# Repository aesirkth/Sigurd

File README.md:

# Sigurd
Propulsion Sensor Unit

# Prerequisites
Follow [zephyr getting started guide](https://docs.zephyrproject.org/latest/develop/getting_started/index.html)

# Build 

```bash
cd zephyr-firmware
west update
cd sigurd
west build -b sigurd app --pristine
west flash
```

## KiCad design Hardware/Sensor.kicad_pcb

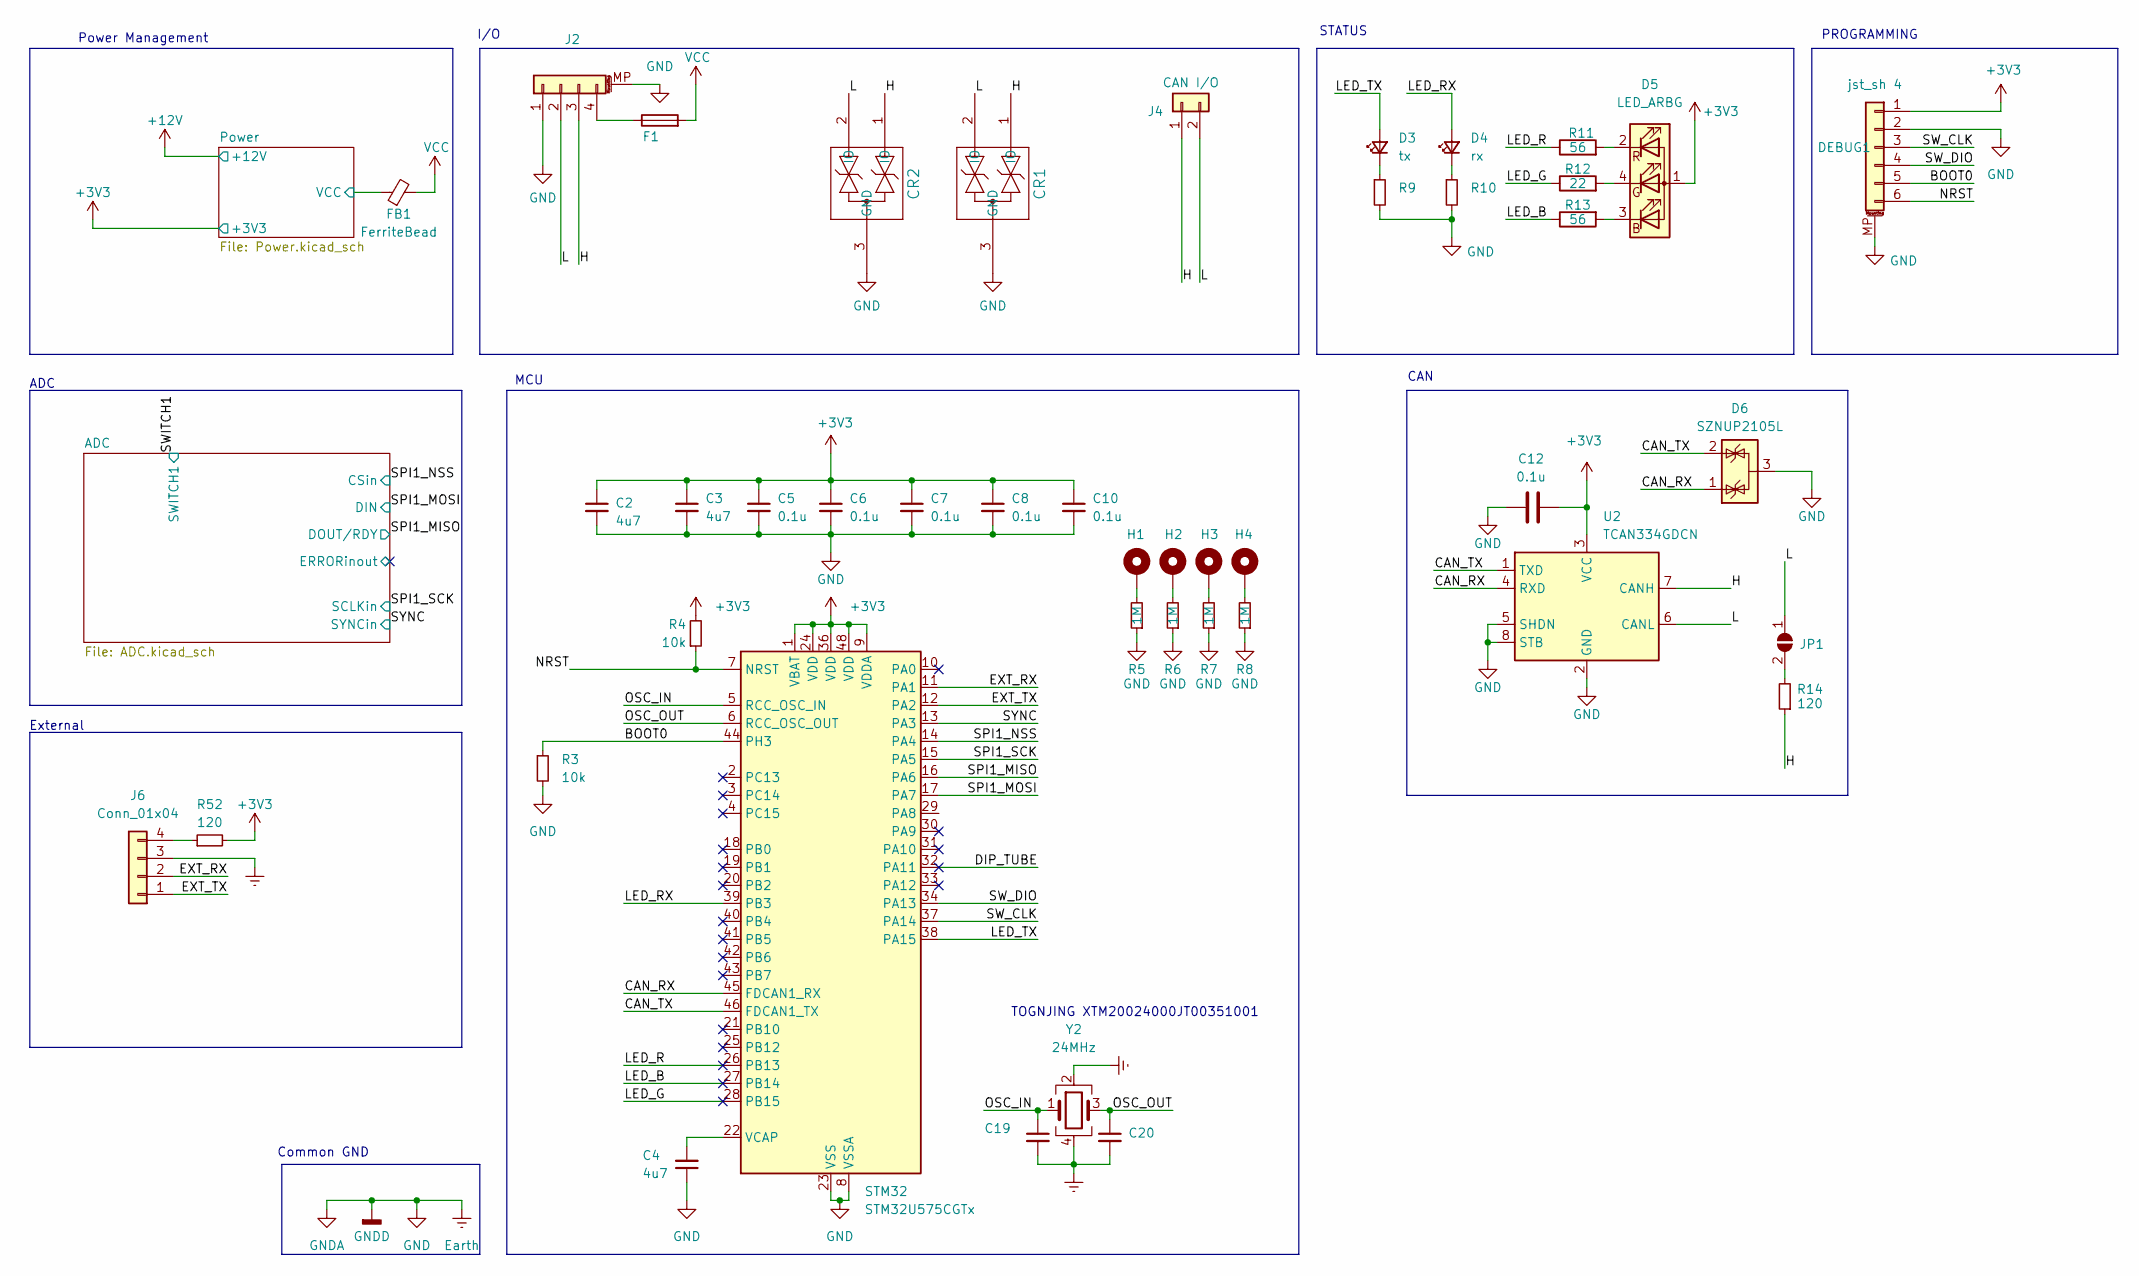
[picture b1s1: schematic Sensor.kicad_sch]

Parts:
C2, C3, C4: 4u7; C_0402_1005Metric
C5, C6, C7, C8, C10, C12: 0.1u; C_0402_1005Metric
C19, C20: 18p; C_0402_1005Metric
CR1, CR2: ESD2CAN36DBZRQ1; SOT-23-3
D3: tx; LED_0603_1608Metric_Pad1.05x0.95mm_HandSolder
D4: rx; LED_0603_1608Metric_Pad1.05x0.95mm_HandSolder
D5: LED_ARBG; LED_Lumex_SML-LX0404SIUPGUSB
D6: SZNUP2105L; SOT-23
DEBUG1: jst_sh 4; JST_SH_SM06B-SRSS-TB_1x06-1MP_P1.00mm_Horizontal
F1: Fuse_1206_3216Metric
FB1: FerriteBead; L_0603_1608Metric
H1, H2, H3, H4: MountingHole_Pad; MountingHole_3.2mm_M3_Pad_Via
J2: Conn_01x04_MountingPin; JST_GH_BM04B-GHS-TBT_1x04-1MP_P1.25mm_Vertical
J4: CAN I/O; JST_XH_B2B-XH-A_1x02_P2.50mm_Vertical
J6: Conn_01x04; PinSocket_1x04_P1.27mm_Vertical
JP1: SolderJumper_2_Open; SolderJumper-2_P1.3mm_Open_TrianglePad1.0x1.5mm
R3, R4: 10k; R_0402_1005Metric
R5, R6, R7, R8: 1M; R_0603_1608Metric_Pad0.98x0.95mm_HandSolder
R9, R10: 330; R_0603_1608Metric_Pad0.98x0.95mm_HandSolder
R11, R13: 56; R_0603_1608Metric_Pad0.98x0.95mm_HandSolder
R12: 22; R_0603_1608Metric_Pad0.98x0.95mm_HandSolder
R14: 120; R_0603_1608Metric_Pad0.98x0.95mm_HandSolder
R52: 120; R_0402_1005Metric
STM32: STM32U575CGTx; LQFP-48_7x7mm_P0.5mm
U2: TCAN334GDCN; TSOT-23-8
Y2: 24MHz; Crystal_SMD_2016-4Pin_2.0x1.6mm

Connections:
+3V3: C2.1, C3.1, C5.1, C6.1, C7.1, C8.1, C10.1, C12.2, D5.1 (A), DEBUG1.1, R4.2, R52.2, STM32.1 (VBAT), STM32.9 (VDDA), STM32.24 (VDD), STM32.36 (VDD), STM32.48 (VDD), U2.3 (VCC); also elsewhere on the board
+12V: FB1.1; also elsewhere on the board
/BOOT0: DEBUG1.5, R3.1, STM32.44 (PH3)
/CAN_RX: D6.1 (K), STM32.45 (FDCAN1_RX), U2.4 (RXD)
/CAN_TX: D6.2 (K), STM32.46 (FDCAN1_TX), U2.1 (TXD)
/DIP_TUBE: STM32.32 (PA11)
/EXT_RX: J6.2, STM32.11 (PA1)
/EXT_TX: J6.1, STM32.12 (PA2)
/H: CR1.1 (IO), CR2.1 (IO), J2.3, J4.1, R14.1, U2.7 (CANH)
/L: CR1.2 (IO), CR2.2 (IO), J2.2, J4.2, JP1.1 (A), U2.6 (CANL)
/LED_B: R13.1, STM32.27 (PB14)
/LED_G: R12.1, STM32.28 (PB15)
/LED_R: R11.1, STM32.26 (PB13)
/LED_RX: D4.2 (A), STM32.39 (PB3)
/LED_TX: D3.2 (A), STM32.38 (PA15)
/NRST: DEBUG1.6, R4.1, STM32.7 (NRST)
/OSC_IN: C19.1, STM32.5 (RCC_OSC_IN), Y2.1
/OSC_OUT: C20.1, STM32.6 (RCC_OSC_OUT), Y2.3
/SPI1_MISO: STM32.16 (PA6); also elsewhere on the board
/SPI1_MOSI: STM32.17 (PA7); also elsewhere on the board
/SPI1_NSS: STM32.14 (PA4); also elsewhere on the board
/SPI1_SCK: STM32.15 (PA5); also elsewhere on the board
/SW_CLK: DEBUG1.3, STM32.37 (PA14)
/SW_DIO: DEBUG1.4, STM32.34 (PA13)
/SYNC: STM32.13 (PA3); also elsewhere on the board
Earth: C2.2, C3.2, C4.1, C5.2, C6.2, C7.2, C8.2, C10.2, C12.1, C19.2, C20.2, CR1.3 (GND), CR2.3 (GND), D6.3 (A), DEBUG1.2, DEBUG1.MP (MountPin), J2.1, J2.MP (MountPin), J6.3, R3.2, R5.1, R6.1, R7.1, R8.1, R9.2, R10.2, STM32.8 (VSSA), STM32.23 (VSS), STM32.35 (VSS), STM32.47 (VSS), U2.2 (GND), U2.5 (SHDN), U2.8 (STB), Y2.2, Y2.4; also elsewhere on the board
unnamed: D3.1 (K), R9.1
unnamed: D4.1 (K), R10.1
unnamed: D5.3 (BK), R13.2
unnamed: D5.4 (GK), R12.2
unnamed: D5.2 (RK), R11.2
unnamed: H1.1, R5.2
unnamed: H2.1, R6.2
unnamed: H3.1, R7.2
unnamed: H4.1, R8.2
unnamed: F1.1, J2.4
unnamed: J6.4, R52.1
unnamed: JP1.2 (B), R14.2
unnamed: C4.2, STM32.22 (VCAP)
VCC: F1.2, FB1.2

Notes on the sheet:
MCU
PROGRAMMING
External
STATUS
CAN
ADC
I/O
Power Management
Common GND
TOGNJING XTM20024000JT00351001

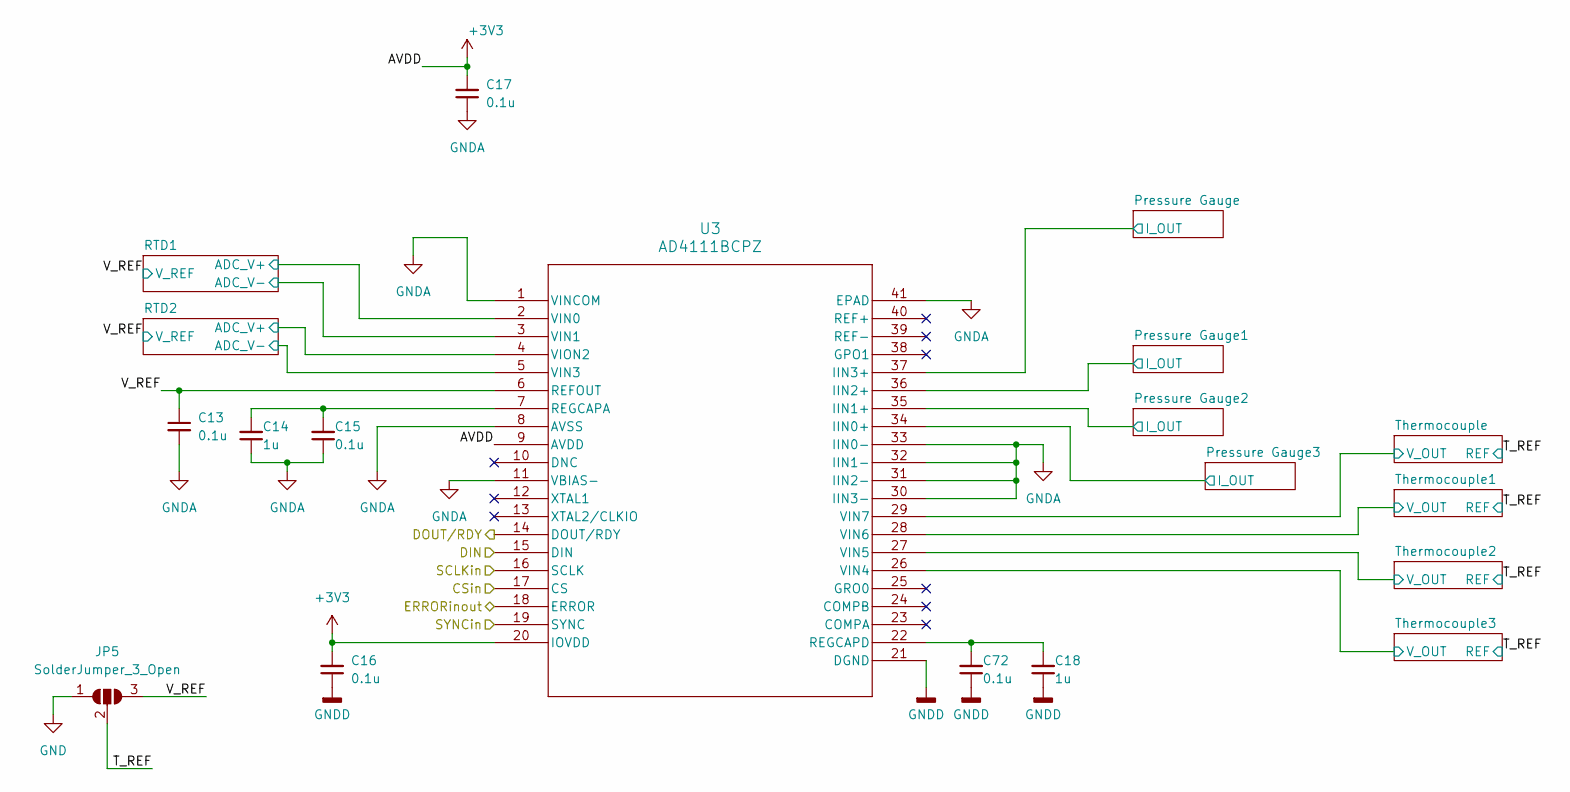
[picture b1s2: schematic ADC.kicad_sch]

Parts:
C13, C15, C16, C17, C72: 0.1u; C_0402_1005Metric
C14, C18: 1u; C_0402_1005Metric
JP5: SolderJumper_3_Open; SolderJumper-3_P1.3mm_Open_Pad1.0x1.5mm_NumberLabels
U3: AD4111BCPZ; AD4111BCPZ_ADI

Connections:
+3V3: C16.2, C17.2, U3.9 (AVDD), U3.20 (IOVDD); also elsewhere on the board
/ADC/ERRORinout: U3.18 (ERROR)
/ADC/Pressure Gauge1/I_OUT: U3.36 (IIN2+); also elsewhere on the board
/ADC/Pressure Gauge2/I_OUT: U3.35 (IIN1+); also elsewhere on the board
/ADC/Pressure Gauge3/I_OUT: U3.34 (IIN0+); also elsewhere on the board
/ADC/Pressure Gauge/I_OUT: U3.37 (IIN3+); also elsewhere on the board
/ADC/RTD1/ADC_V+: U3.2 (VIN0); also elsewhere on the board
/ADC/RTD1/ADC_V-: U3.3 (VIN1); also elsewhere on the board
/ADC/RTD2/ADC_V+: U3.4 (VION2); also elsewhere on the board
/ADC/RTD2/ADC_V-: U3.5 (VIN3); also elsewhere on the board
/ADC/T_REF: JP5.2 (C); also elsewhere on the board
/ADC/Thermocouple1/V_OUT: U3.28 (VIN6); also elsewhere on the board
/ADC/Thermocouple2/V_OUT: U3.27 (VIN5); also elsewhere on the board
/ADC/Thermocouple3/V_OUT: U3.26 (VIN4); also elsewhere on the board
/ADC/Thermocouple/V_OUT: U3.29 (VIN7); also elsewhere on the board
/ADC/V_REF: C13.1, JP5.3 (B), U3.6 (REFOUT); also elsewhere on the board
/SPI1_MISO: U3.14 (DOUT/RDY); also elsewhere on the board
/SPI1_MOSI: U3.15 (DIN); also elsewhere on the board
/SPI1_NSS: U3.17 (CS); also elsewhere on the board
/SPI1_SCK: U3.16 (SCLK); also elsewhere on the board
/SYNC: U3.19 (SYNC); also elsewhere on the board
Earth: C13.2, C14.1, C15.1, C16.1, C17.1, C18.1, C72.1, JP5.1 (A), U3.1 (VINCOM), U3.8 (AVSS), U3.11 (VBIAS-), U3.21 (DGND), U3.30 (IIN3-), U3.31 (IIN2-), U3.32 (IIN1-), U3.33 (IIN0-), U3.41 (EPAD); also elsewhere on the board
unnamed: C14.2, C15.2, U3.7 (REGCAPA)
unnamed: C18.2, C72.2, U3.22 (REGCAPD)

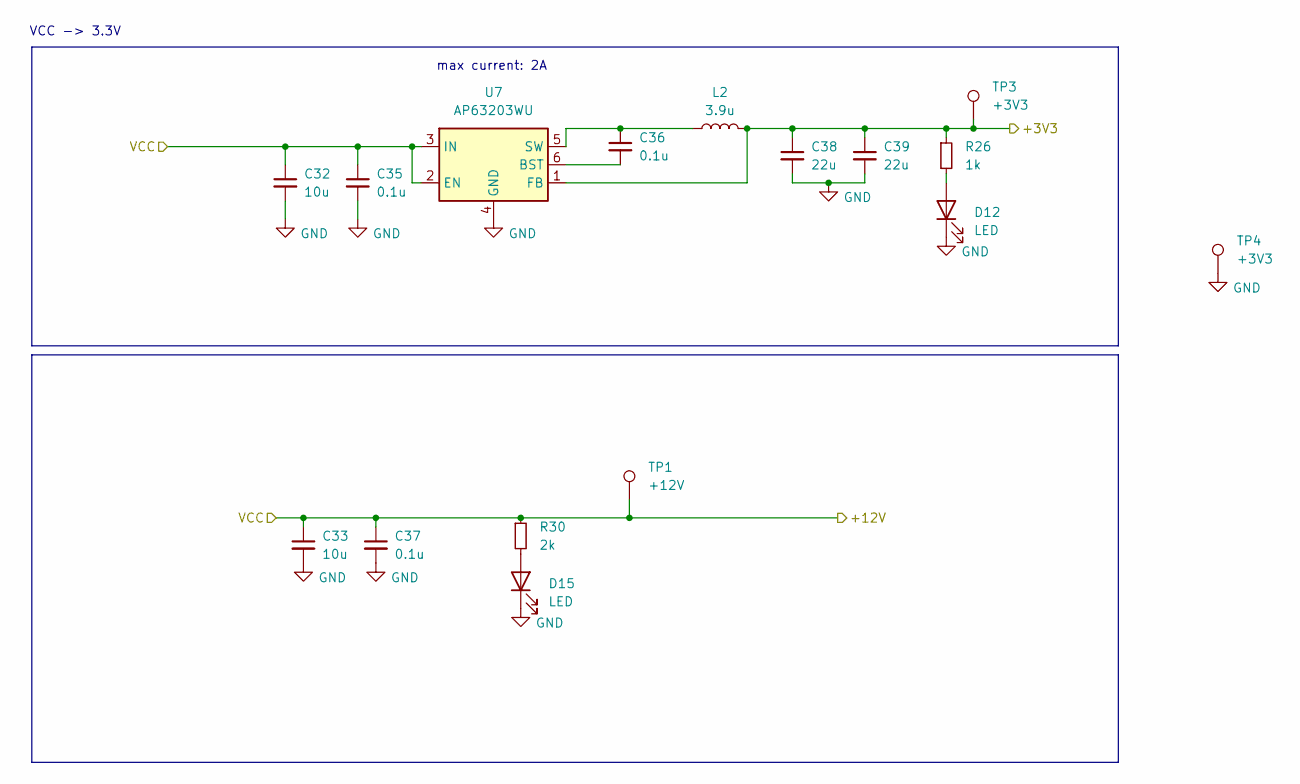
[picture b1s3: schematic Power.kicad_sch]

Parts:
C32, C33: 10u; C_0603_1608Metric
C35, C36, C37: 0.1u; C_0402_1005Metric
C38, C39: 22u; C_0603_1608Metric
D12, D15: LED; D_0603_1608Metric
L2: 3.9u; L_Changjiang_FNR4030S
R26: 1k; R_0603_1608Metric
R30: 2k; R_0603_1608Metric
TP1: +12V; TestPoint_Pad_D2.0mm
TP3, TP4: +3V3; TestPoint_Pad_D2.0mm
U7: AP63203WU; TSOT-23-6

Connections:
+3V3: C38.1, C39.1, L2.2, R26.1, TP3.1, U7.1 (FB); also elsewhere on the board
+12V: C32.1, C33.1, C35.1, C37.1, R30.1, TP1.1, U7.2 (EN), U7.3 (IN); also elsewhere on the board
Earth: C32.2, C33.2, C35.2, C37.2, C38.2, C39.2, D12.1 (K), D15.1 (K), TP4.1, U7.4 (GND); also elsewhere on the board
unnamed: D12.2 (A), R26.2
unnamed: D15.2 (A), R30.2
unnamed: C36.2, U7.6 (BST)
unnamed: C36.1, L2.1, U7.5 (SW)

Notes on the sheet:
max current: 2A
VCC -> 3.3V

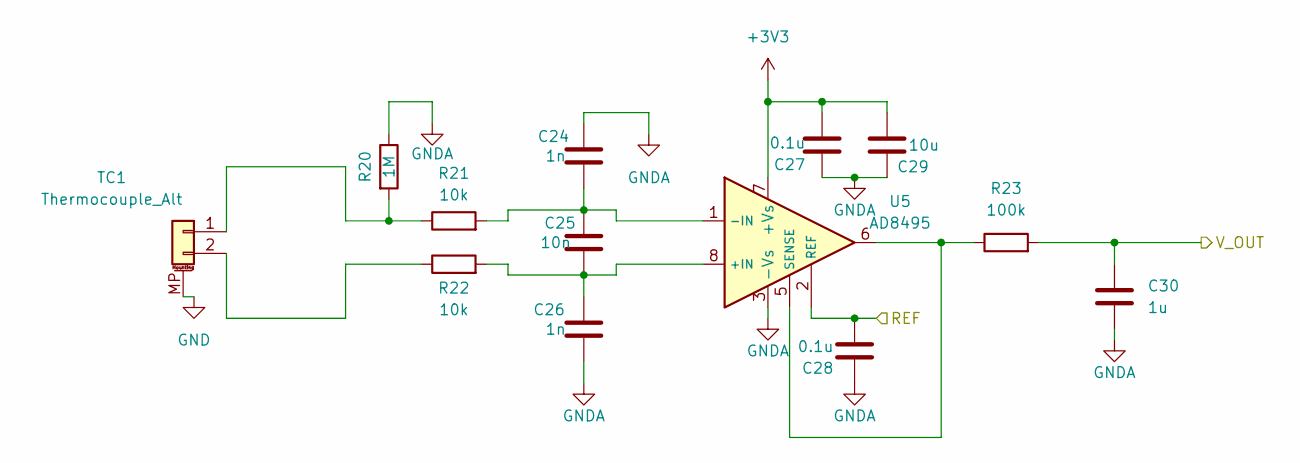
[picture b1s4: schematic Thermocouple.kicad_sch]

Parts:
C24, C26: 1n; C_0603_1608Metric
C25: 10n; C_0603_1608Metric
C27, C28: 0.1u; C_0402_1005Metric
C29: 10u; C_0603_1608Metric
C30: 1u; C_0402_1005Metric
R20: 1M; R_0402_1005Metric
R21, R22: 10k; R_0402_1005Metric
R23: 100k; R_0402_1005Metric
TC1: Thermocouple_Alt; Molex_Micro-Fit_3.0_43650-0210_1x02-1MP_P3.00mm_Horizontal
U5: AD8495; MSOP-8_3x3mm_P0.65mm

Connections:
+3V3: C27.2, C29.2, U5.7 (+Vs); also elsewhere on the board
/ADC/T_REF: C28.2, U5.2 (REF); also elsewhere on the board
/ADC/Thermocouple/V_OUT: C30.1, R23.2; also elsewhere on the board
Earth: C24.1, C26.2, C27.1, C28.1, C29.1, C30.2, R20.1, TC1.MP (MountPin), U5.3 (-Vs); also elsewhere on the board
unnamed: R20.2, R21.1, TC1.1
unnamed: R22.1, TC1.2
unnamed: C25.2, C26.1, R22.2, U5.8 (+IN)
unnamed: C24.2, C25.1, R21.2, U5.1 (-IN)
unnamed: R23.1, U5.5 (SENSE), U5.6

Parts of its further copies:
C46, C48, C53, C55, C60, C62: 1n; C_0603_1608Metric
C47, C54, C61: 10n; C_0603_1608Metric
C49, C50, C56, C57, C63, C64: 0.1u; C_0402_1005Metric
C51, C58, C65: 10u; C_0603_1608Metric
C52, C59, C66: 1u; C_0402_1005Metric
R31, R35, R39: 1M; R_0402_1005Metric
R32, R33, R36, R37, R40, R41: 10k; R_0402_1005Metric
R34, R38, R42: 100k; R_0402_1005Metric
TC2, TC3, TC4: Thermocouple_Alt; Molex_Micro-Fit_3.0_43650-0210_1x02-1MP_P3.00mm_Horizontal
U9, U10, U11: AD8495; MSOP-8_3x3mm_P0.65mm

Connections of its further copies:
+3V3: C49.2, C51.2, C56.2, C58.2, C63.2, C65.2, U9.7 (+Vs), U10.7 (+Vs), U11.7 (+Vs); also elsewhere on the board
/ADC/T_REF: C50.2, C57.2, C64.2, U9.2 (REF), U10.2 (REF), U11.2 (REF); also elsewhere on the board
/ADC/Thermocouple1/V_OUT: C52.1, R34.2; also elsewhere on the board
/ADC/Thermocouple2/V_OUT: C59.1, R38.2; also elsewhere on the board
/ADC/Thermocouple3/V_OUT: C66.1, R42.2; also elsewhere on the board
Earth: C46.1, C48.2, C49.1, C50.1, C51.1, C52.2, C53.1, C55.2, C56.1, C57.1, C58.1, C59.2, C60.1, C62.2, C63.1, C64.1, C65.1, C66.2, R31.1, R35.1, R39.1, TC2.MP (MountPin), TC3.MP (MountPin), TC4.MP (MountPin), U9.3 (-Vs), U10.3 (-Vs), U11.3 (-Vs); also elsewhere on the board
unnamed: R31.2, R32.1, TC2.1
unnamed: R33.1, TC2.2
unnamed: R35.2, R36.1, TC3.1
unnamed: R37.1, TC3.2
unnamed: R39.2, R40.1, TC4.1
unnamed: R41.1, TC4.2
unnamed: C47.2, C48.1, R33.2, U9.8 (+IN)
unnamed: C46.2, C47.1, R32.2, U9.1 (-IN)
unnamed: R34.1, U9.5 (SENSE), U9.6
unnamed: C54.2, C55.1, R37.2, U10.8 (+IN)
unnamed: C53.2, C54.1, R36.2, U10.1 (-IN)
unnamed: R38.1, U10.5 (SENSE), U10.6
unnamed: C61.2, C62.1, R41.2, U11.8 (+IN)
unnamed: C60.2, C61.1, R40.2, U11.1 (-IN)
unnamed: R42.1, U11.5 (SENSE), U11.6

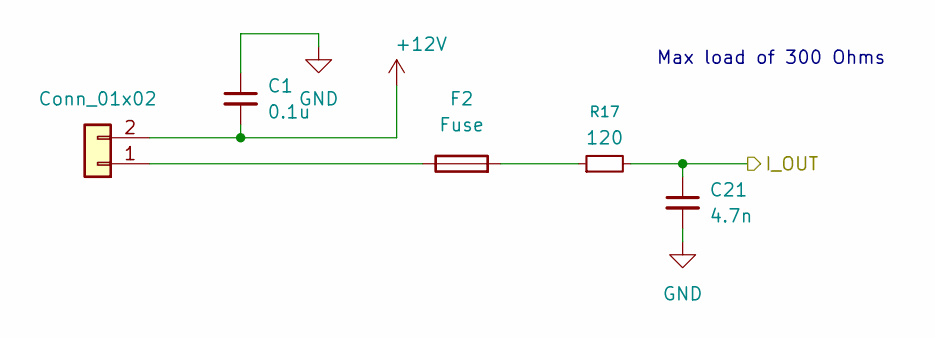
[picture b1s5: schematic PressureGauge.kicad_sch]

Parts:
C1: 0.1u; C_0603_1608Metric
C21: 4.7n; C_0402_1005Metric
F2: Fuse; Fuse_0603_1608Metric_Pad1.05x0.95mm_HandSolder
J1: Conn_01x02; JST_PH_B2B-PH-K_1x02_P2.00mm_Vertical
R17: 120; R_0402_1005Metric

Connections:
+12V: C1.2, J1.2; also elsewhere on the board
/ADC/Pressure Gauge1/I_OUT: C21.1, R17.2; also elsewhere on the board
Earth: C1.1, C21.2; also elsewhere on the board
unnamed: F2.2, R17.1
unnamed: F2.1, J1.1

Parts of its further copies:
C9, C11, C31: 0.1u; C_0603_1608Metric
C22, C23, C40: 4.7n; C_0402_1005Metric
F4, F6, F8: Fuse; Fuse_0603_1608Metric_Pad1.05x0.95mm_HandSolder
J3, J5, J7: Conn_01x02; JST_PH_B2B-PH-K_1x02_P2.00mm_Vertical
R18, R19, R27: 120; R_0402_1005Metric

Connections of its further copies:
+12V: C9.2, C11.2, C31.2, J3.2, J5.2, J7.2; also elsewhere on the board
/ADC/Pressure Gauge2/I_OUT: C22.1, R18.2; also elsewhere on the board
/ADC/Pressure Gauge3/I_OUT: C23.1, R19.2; also elsewhere on the board
/ADC/Pressure Gauge/I_OUT: C40.1, R27.2; also elsewhere on the board
Earth: C9.1, C11.1, C22.2, C23.2, C31.1, C40.2; also elsewhere on the board
unnamed: F4.2, R18.1
unnamed: F6.2, R19.1
unnamed: F8.2, R27.1
unnamed: F4.1, J3.1
unnamed: F6.1, J5.1
unnamed: F8.1, J7.1

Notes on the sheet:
Max load of 300 Ohms

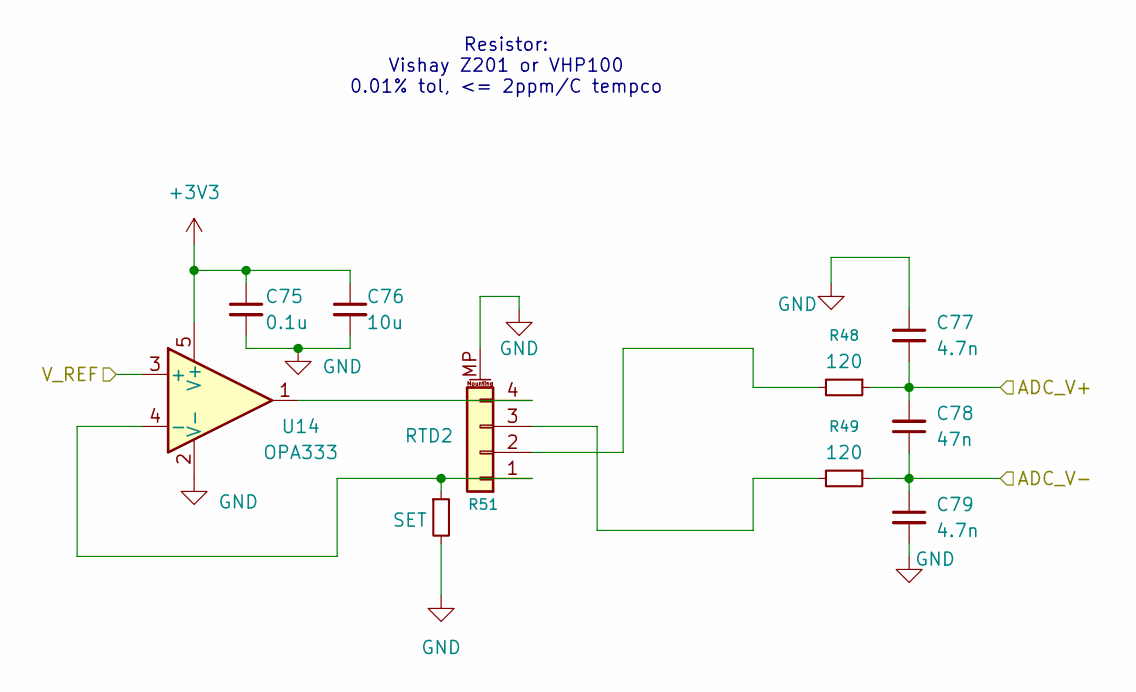
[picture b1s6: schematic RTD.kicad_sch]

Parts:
C75: 0.1u; C_0402_1005Metric
C76: 10u; C_0603_1608Metric
C77, C79: 4.7n; C_0402_1005Metric
C78: 47n; C_0402_1005Metric
R48, R49: 120; R_0402_1005Metric
R51: SET; R_0603_1608Metric_Pad0.98x0.95mm_HandSolder
RTD2: Conn_01x04_MountingPin; JST_GH_SM04B-GHS-TB_1x04-1MP_P1.25mm_Horizontal
U14: OPA333; SOT-23-5_HandSoldering

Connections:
+3V3: C75.1, C76.1, U14.5 (V+); also elsewhere on the board
/ADC/RTD2/ADC_V+: C77.2, C78.2, R48.1; also elsewhere on the board
/ADC/RTD2/ADC_V-: C78.1, C79.1, R49.1; also elsewhere on the board
/ADC/V_REF: U14.3 (+); also elsewhere on the board
Earth: C75.2, C76.2, C77.1, C79.2, R51.2, RTD2.MP (MountPin), U14.2 (V-); also elsewhere on the board
unnamed: R51.1, RTD2.1, U14.4 (-)
unnamed: R48.2, RTD2.2
unnamed: R49.2, RTD2.3
unnamed: RTD2.4, U14.1

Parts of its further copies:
C67: 0.1u; C_0402_1005Metric
C68: 10u; C_0603_1608Metric
C69, C71: 4.7n; C_0402_1005Metric
C70: 47n; C_0402_1005Metric
R28, R44: 120; R_0402_1005Metric
R50: SET; R_0603_1608Metric_Pad0.98x0.95mm_HandSolder
RTD1: Conn_01x04_MountingPin; JST_GH_SM04B-GHS-TB_1x04-1MP_P1.25mm_Horizontal
U12: OPA333; SOT-23-5_HandSoldering

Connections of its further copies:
+3V3: C67.1, C68.1, U12.5 (V+); also elsewhere on the board
/ADC/RTD1/ADC_V+: C69.2, C70.2, R44.1; also elsewhere on the board
/ADC/RTD1/ADC_V-: C70.1, C71.1, R28.1; also elsewhere on the board
/ADC/V_REF: U12.3 (+); also elsewhere on the board
Earth: C67.2, C68.2, C69.1, C71.2, R50.2, RTD1.MP (MountPin), U12.2 (V-); also elsewhere on the board
unnamed: R50.1, RTD1.1, U12.4 (-)
unnamed: R44.2, RTD1.2
unnamed: R28.2, RTD1.3
unnamed: RTD1.4, U12.1

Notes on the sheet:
Resistor: Vishay Z201 or VHP100 0.01% tol, <= 2ppm/C tempco

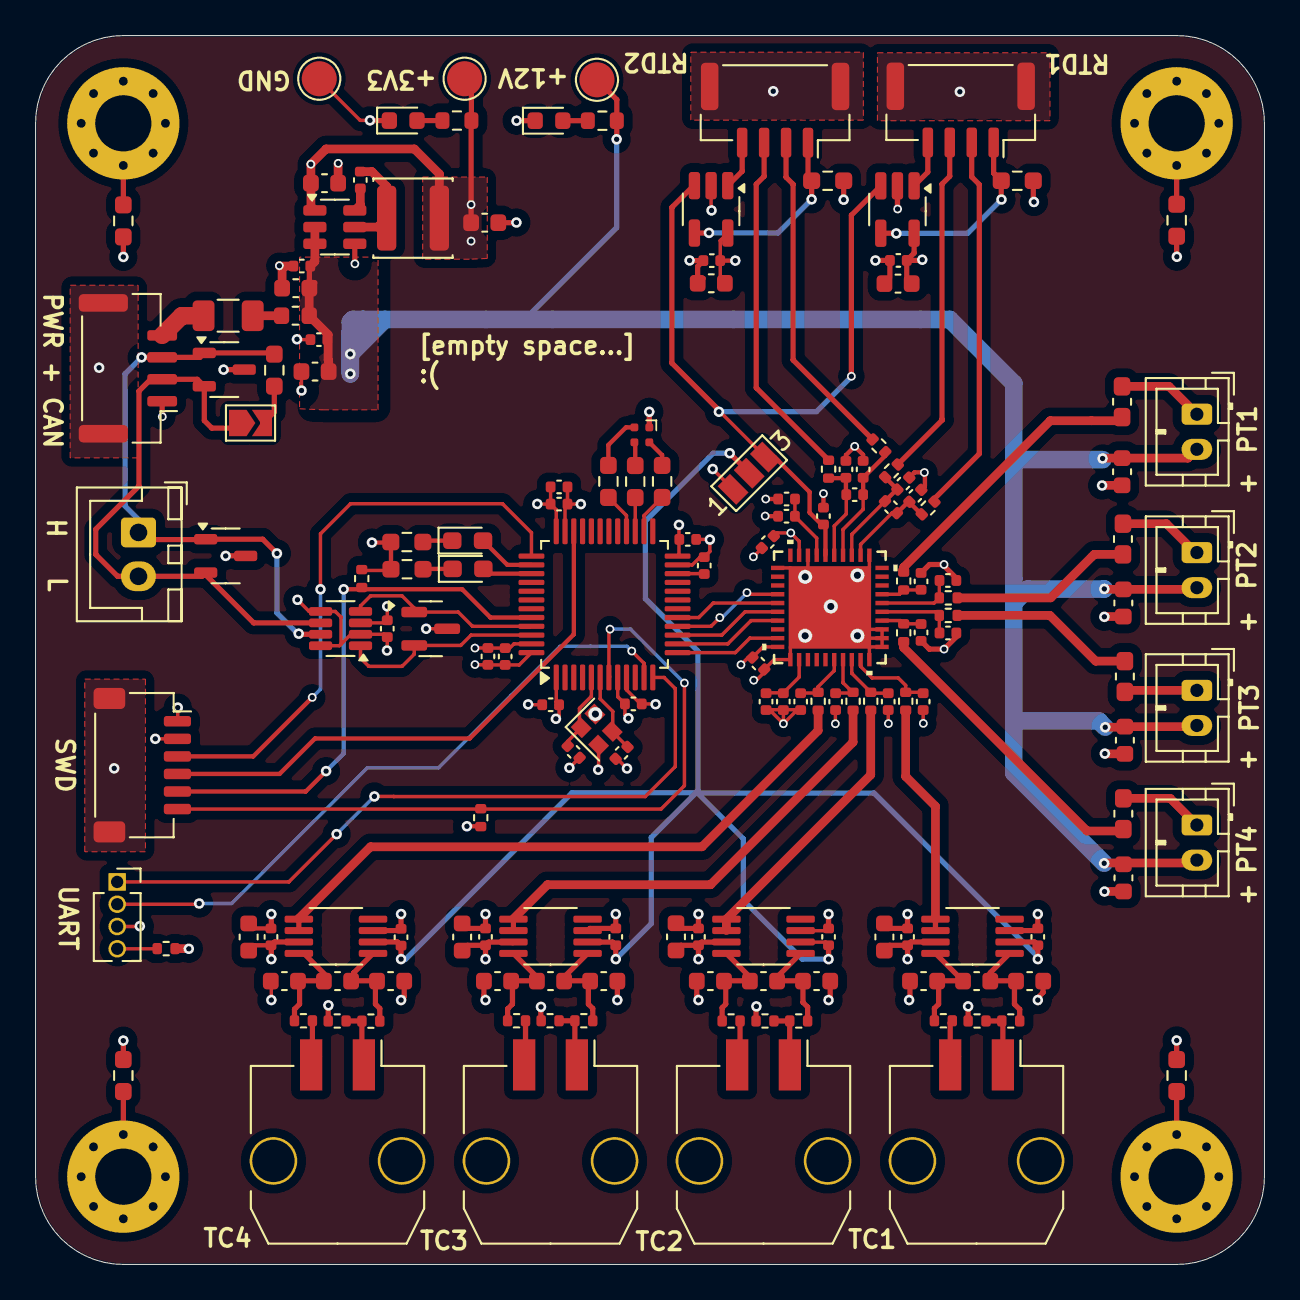
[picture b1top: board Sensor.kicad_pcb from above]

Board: 4 copper layers, 70.0 x 70.0 mm, 161 parts (0 on the bottom side), 95 nets.

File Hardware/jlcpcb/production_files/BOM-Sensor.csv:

Comment,Designator,Footprint,LCSC,Quantity
1k,R26,R_0603_1608Metric,C11702,1
0.1u,"C1,C11,C31,C9",C_0603_1608Metric,C14663,4
FerriteBead,FB1,L_0603_1608Metric,C14709,1
4.7n,"C21,C22,C23,C40,C69,C71,C77,C79",C_0402_1005Metric,C1538,8
18p,"C19,C20",C_0402_1005Metric,C1549,2
1n,"C24,C26,C46,C48,C53,C55,C60,C62",C_0603_1608Metric,C1588,8
3.9u,L2,L_Changjiang_FNR4030S,C167872,1
TCAN334GDCN,U2,TSOT-23-8,C191005,1
LED,D12,D_0603_1608Metric,C19171301,1
rx,D4,LED_0603_1608Metric_Pad1.05x0.95mm_HandSolder,C2286,1
LED,D15,D_0603_1608Metric,C2288,1
tx,D3,LED_0603_1608Metric_Pad1.05x0.95mm_HandSolder,C2290,1
1M,"R5,R6,R7,R8",R_0603_1608Metric_Pad0.98x0.95mm_HandSolder,C22935,4
2k,R30,R_0603_1608Metric,C22975,1
SZNUP2105L,D6,SOT-23,C23083861,1
330,"R10,R9",R_0603_1608Metric_Pad0.98x0.95mm_HandSolder,C23138,2
4u7,"C2,C3,C4",C_0402_1005Metric,C23733,3
120,"R17,R18,R19,R27,R28,R44,R48,R49,R52",R_0402_1005Metric,C25079,9
100k,"R23,R34,R38,R42",R_0402_1005Metric,C25741,4
10k,"R21,R22,R3,R32,R33,R36,R37,R4,R40,R41",R_0402_1005Metric,C25744,10
1M,"R20,R31,R35,R39",R_0402_1005Metric,C26083,4
ESD2CAN36DBZRQ1,"CR1,CR2",SOT-23-3,C284078,2
0.1u,"C10,C12,C13,C15,C16,C17,C27,C28,C35,C36,C37,C49,C5,C50,C56,C57,C6,C63,C64,C67,C7,C72,C75,C8",C_0402_1005Metric,C307331,24
OPA333,"U12,U14",SOT-23-5_HandSoldering,C30878,2
24MHz,Y2,Crystal_SMD_2016-4Pin_2.0x1.6mm,C37635323,1
1u,"C14,C18,C30,C52,C59,C66",C_0402_1005Metric,C52923,6
10n,"C25,C47,C54,C61",C_0603_1608Metric,C57112,4
22u,"C38,C39",C_0603_1608Metric,C59461,2
AD8495,"U10,U11,U5,U9",MSOP-8_3x3mm_P0.65mm,C59658,4
AD4111BCPZ,U3,AD4111BCPZ_ADI,C649166,1
AP63203WU,U7,TSOT-23-6,C780769,1
47n,"C70,C78",C_0402_1005Metric,C82219,2
10u,"C29,C32,C33,C51,C58,C65,C68,C76",C_0603_1608Metric,C96446,8

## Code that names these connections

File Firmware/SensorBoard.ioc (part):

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Mcu.Name=STM32U575CGTx
Mcu.Package=LQFP48
Mcu.UserName=STM32U575CGTx
PA10.Signal=GPIO_Output
PA13\ (JTMS/SWDIO).Mode=Serial_Wire
PA13\ (JTMS/SWDIO).Signal=DEBUG_JTMS-SWDIO
PA14\ (JTCK/SWCLK).Mode=Serial_Wire
PA14\ (JTCK/SWCLK).Signal=DEBUG_JTCK-SWCLK
PA15\ (JTDI).Signal=GPIO_Output
PA4.GPIOParameters=PinState
PA4.PinState=GPIO_PIN_SET
PA4.Signal=GPIO_Output
PA5.Mode=Full_Duplex_Master
PA5.Signal=SPI1_SCK
PA6.Mode=Full_Duplex_Master
PA6.Signal=SPI1_MISO
PA7.Mode=Full_Duplex_Master
PA7.Signal=SPI1_MOSI
PA8.Signal=GPIO_Output
PA9.Signal=GPIO_Output
PB12.Signal=GPIO_Output
PB3\ (JTDO/TRACESWO).Signal=GPIO_Output
PB5.Signal=GPIO_Output
PH0-OSC_IN\ (PH0).Mode=HSE-External-Oscillator
PH0-OSC_IN\ (PH0).Signal=RCC_OSC_IN
PH1-OSC_OUT\ (PH1).Mode=HSE-External-Oscillator
PH1-OSC_OUT\ (PH1).Signal=RCC_OSC_OUT
RCC.HSE_VALUE=16000000
RCC.SYSCLKFreq_VALUE=64000000
RCC.SYSCLKSource=RCC_SYSCLKSOURCE_PLLCLK
board=custom

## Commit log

2025-10-11 added hardware folder
2025-10-11 Added firmware folder
2025-11-24 sigurd redesign :)
2025-11-24 pushed wrong hardware revision
2025-12-04 Zephyr Sigurd Support
2025-12-10 west build works
2025-12-10 added can but did not test build
2025-12-10 stuff
2025-12-10 added ad4111 module
2025-12-10 reading something from ADC but possibly not correct values
2025-12-16 added spi.c setup for ADC driver
2025-12-16 spi test
2026-01-21 spi testing things
2026-01-21 spi read register now works
2026-01-22 sigurd can now read spi from ADC
2026-01-24 most recent sigurd code
2026-01-27 hardcoded a pseudo-adc driver
2026-01-28 MISO interrupt now works
2026-01-28 cleaned up some stuff
2026-02-04 interrupt and reading valid data with integer flag
2026-02-04 reading valid data with interrupt and semaphore
2026-02-23 sigurd is sending CAN and doing a running average every 5 seconds
2026-02-23 added a lil todo
2026-02-27 reading degrees from RTD?!
2026-03-03 deleting useless files
